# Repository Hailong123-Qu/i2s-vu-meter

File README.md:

Doesn't parse data during RMS calculation for about 108 ms

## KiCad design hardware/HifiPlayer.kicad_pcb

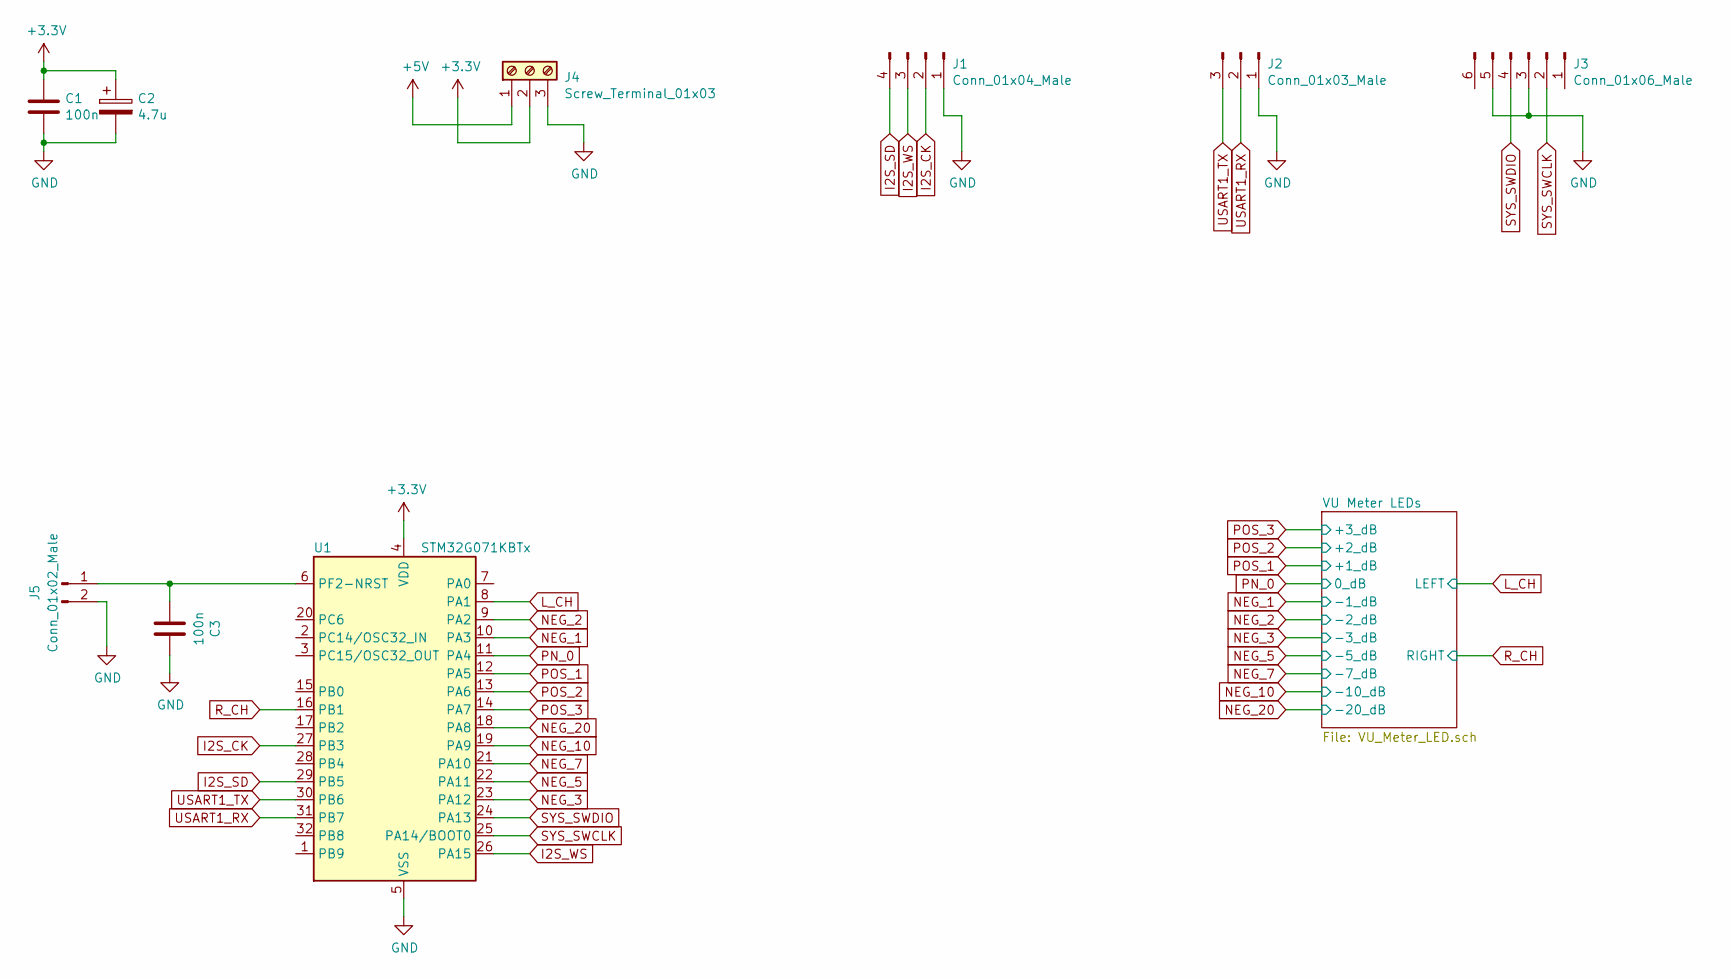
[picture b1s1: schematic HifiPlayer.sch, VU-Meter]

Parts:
C1, C3: 100n; C_1206_3216Metric_Pad1.42x1.75mm_HandSolder
C2: 4.7u; CP_Radial_D5.0mm_P2.00mm
J1: Conn_01x04_Male; PinHeader_1x04_P2.54mm_Vertical
J2: Conn_01x03_Male; PinHeader_1x03_P2.54mm_Vertical
J3: Conn_01x06_Male; PinHeader_1x06_P2.54mm_Vertical
J4: Screw_Terminal_01x03; TerminalBlock_bornier-3_P5.08mm
J5: Conn_01x02_Male; PinHeader_1x02_P2.54mm_Vertical
U1: STM32G071KBTx; LQFP-32_7x7mm_P0.8mm

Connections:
+3V3: C1.1, C2.1, J4.2, U1.4 (VDD)
+5V: J4.1; also elsewhere on the board
GND: C1.2, C2.2, C3.1, J1.1, J2.1, J3.3, J3.5, J4.3, J5.2, U1.5 (VSS); also elsewhere on the board
I2S_CK: J1.2, U1.27 (PB3)
I2S_SD: J1.4, U1.29 (PB5)
I2S_WS: J1.3, U1.26 (PA15)
L_CH: U1.8 (PA1); also elsewhere on the board
NEG_1: U1.10 (PA3); also elsewhere on the board
NEG_2: U1.9 (PA2); also elsewhere on the board
NEG_3: U1.23 (PA12); also elsewhere on the board
NEG_5: U1.22 (PA11); also elsewhere on the board
NEG_7: U1.21 (PA10); also elsewhere on the board
NEG_10: U1.19 (PA9); also elsewhere on the board
NEG_20: U1.18 (PA8); also elsewhere on the board
unnamed: C3.2, J5.1, U1.6 (PF2-NRST)
PN_0: U1.11 (PA4); also elsewhere on the board
POS_1: U1.12 (PA5); also elsewhere on the board
POS_2: U1.13 (PA6); also elsewhere on the board
POS_3: U1.14 (PA7); also elsewhere on the board
R_CH: U1.16 (PB1); also elsewhere on the board
SYS_SWCLK: J3.2, U1.25 (PA14/BOOT0)
SYS_SWDIO: J3.4, U1.24 (PA13)
USART1_RX: J2.2, U1.31 (PB7)
USART1_TX: J2.3, U1.30 (PB6)

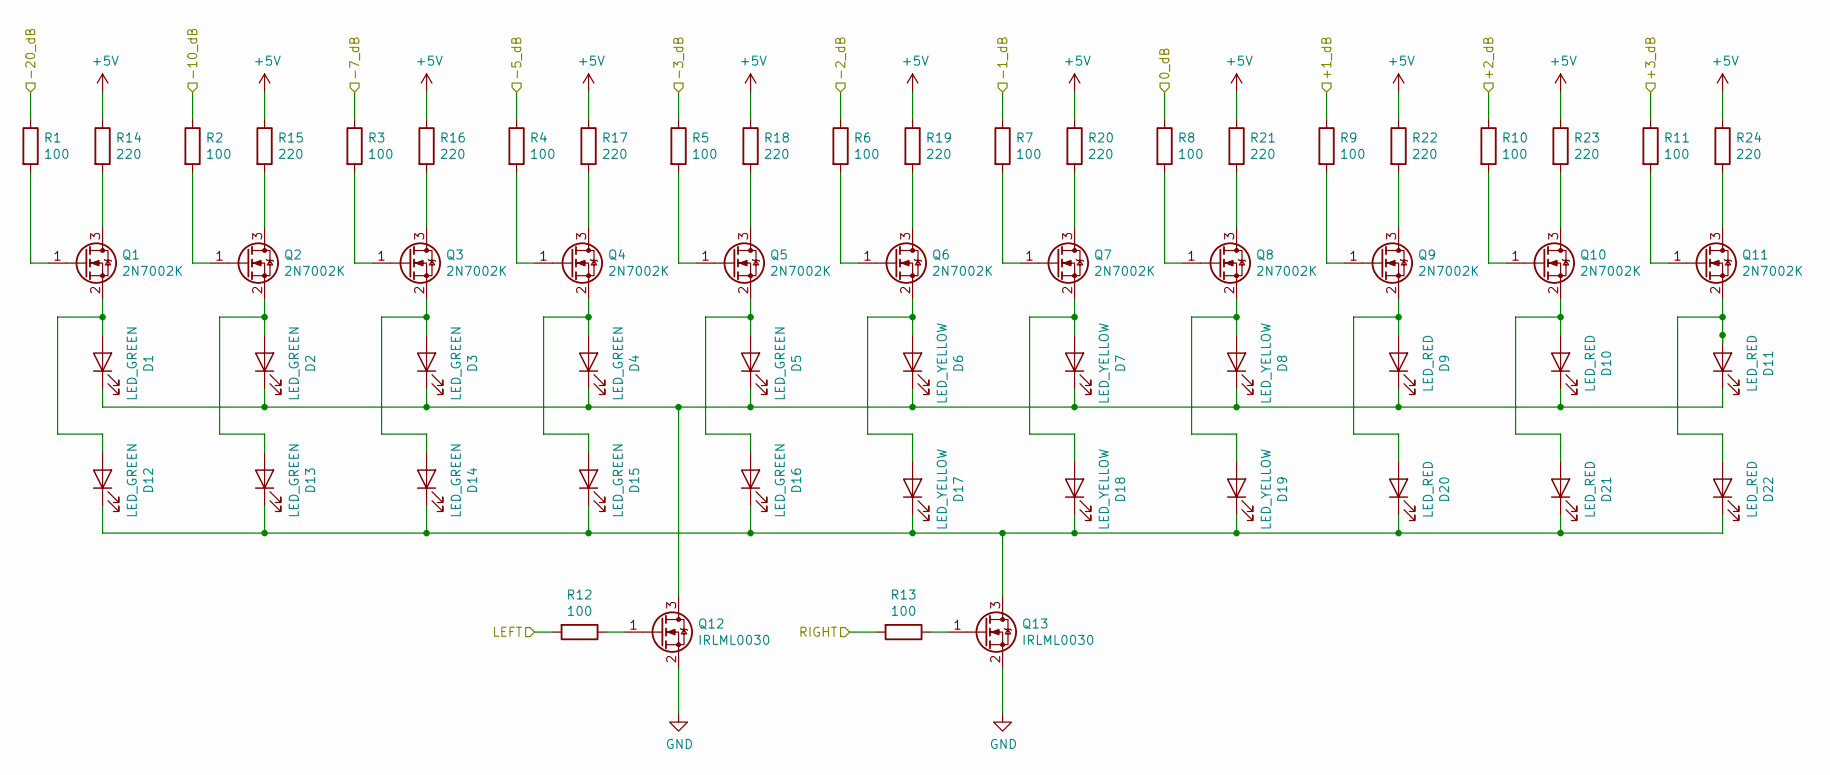
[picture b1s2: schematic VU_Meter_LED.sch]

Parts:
D1, D2, D3, D4, D5, D12, D13, D14, D15, D16: LED_GREEN; LED_D5.0mm
D6, D7, D8, D17, D18, D19: LED_YELLOW; LED_D5.0mm
D9, D10, D11, D20, D21, D22: LED_RED; LED_D5.0mm
Q1, Q2, Q3, Q4, Q5, Q6, Q7, Q8, Q9, Q10, Q11: 2N7002K; SOT-23_Handsoldering
Q12, Q13: IRLML0030; SOT-23_Handsoldering
R1, R2, R3, R4, R5, R6, R7, R8, R9, R10, R11, R12, R13: 100; R_1206_3216Metric_Pad1.42x1.75mm_HandSolder
R14, R15, R16, R17, R18, R19, R20, R21, R22, R23, R24: 220; R_Axial_DIN0207_L6.3mm_D2.5mm_P10.16mm_Horizontal

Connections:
+5V: R14.1, R15.1, R16.1, R17.1, R18.1, R19.1, R20.1, R21.1, R22.1, R23.1, R24.1; also elsewhere on the board
GND: Q12.2 (S), Q13.2 (S); also elsewhere on the board
L_CH: R12.2; also elsewhere on the board
NEG_1: R7.1; also elsewhere on the board
NEG_2: R6.1; also elsewhere on the board
NEG_3: R5.1; also elsewhere on the board
NEG_5: R4.1; also elsewhere on the board
NEG_7: R3.1; also elsewhere on the board
NEG_10: R2.1; also elsewhere on the board
NEG_20: R1.1; also elsewhere on the board
unnamed: D1.1 (K), D2.1 (K), D3.1 (K), D4.1 (K), D5.1 (K), D6.1 (K), D7.1 (K), D8.1 (K), D9.1 (K), D10.1 (K), D11.1 (K), Q12.3 (D)
unnamed: D1.2 (A), D12.2 (A), Q1.2 (S)
unnamed: D10.2 (A), D21.2 (A), Q10.2 (S)
unnamed: D11.2 (A), D22.2 (A), Q11.2 (S)
unnamed: D12.1 (K), D13.1 (K), D14.1 (K), D15.1 (K), D16.1 (K), D17.1 (K), D18.1 (K), D19.1 (K), D20.1 (K), D21.1 (K), D22.1 (K), Q13.3 (D)
unnamed: D2.2 (A), D13.2 (A), Q2.2 (S)
unnamed: D3.2 (A), D14.2 (A), Q3.2 (S)
unnamed: D4.2 (A), D15.2 (A), Q4.2 (S)
unnamed: D5.2 (A), D16.2 (A), Q5.2 (S)
unnamed: D6.2 (A), D17.2 (A), Q6.2 (S)
unnamed: D7.2 (A), D18.2 (A), Q7.2 (S)
unnamed: D8.2 (A), D19.2 (A), Q8.2 (S)
unnamed: D9.2 (A), D20.2 (A), Q9.2 (S)
unnamed: Q1.1 (G), R1.2
unnamed: Q1.3 (D), R14.2
unnamed: Q2.1 (G), R2.2
unnamed: Q2.3 (D), R15.2
unnamed: Q3.1 (G), R3.2
unnamed: Q3.3 (D), R16.2
unnamed: Q4.1 (G), R4.2
unnamed: Q4.3 (D), R17.2
unnamed: Q5.1 (G), R5.2
unnamed: Q5.3 (D), R18.2
unnamed: Q6.1 (G), R6.2
unnamed: Q6.3 (D), R19.2
unnamed: Q7.1 (G), R7.2
unnamed: Q7.3 (D), R20.2
unnamed: Q8.1 (G), R8.2
unnamed: Q8.3 (D), R21.2
unnamed: Q9.1 (G), R9.2
unnamed: Q9.3 (D), R22.2
unnamed: Q10.1 (G), R10.2
unnamed: Q10.3 (D), R23.2
unnamed: Q11.1 (G), R11.2
unnamed: Q11.3 (D), R24.2
unnamed: Q12.1 (G), R12.1
unnamed: Q13.1 (G), R13.1
PN_0: R8.1; also elsewhere on the board
POS_1: R9.1; also elsewhere on the board
POS_2: R10.1; also elsewhere on the board
POS_3: R11.1; also elsewhere on the board
R_CH: R13.2; also elsewhere on the board

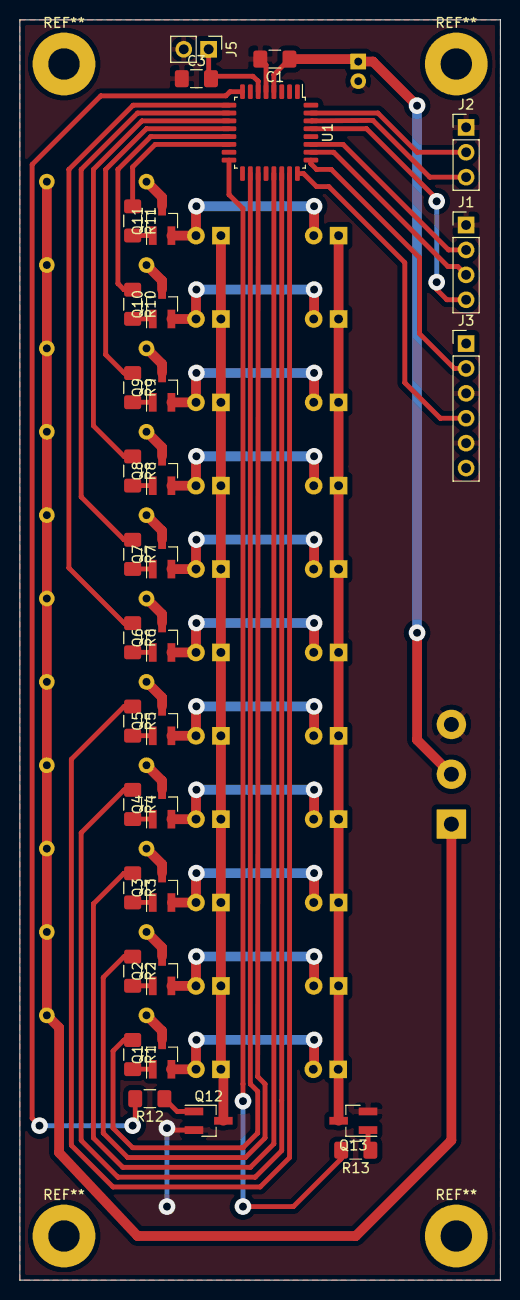
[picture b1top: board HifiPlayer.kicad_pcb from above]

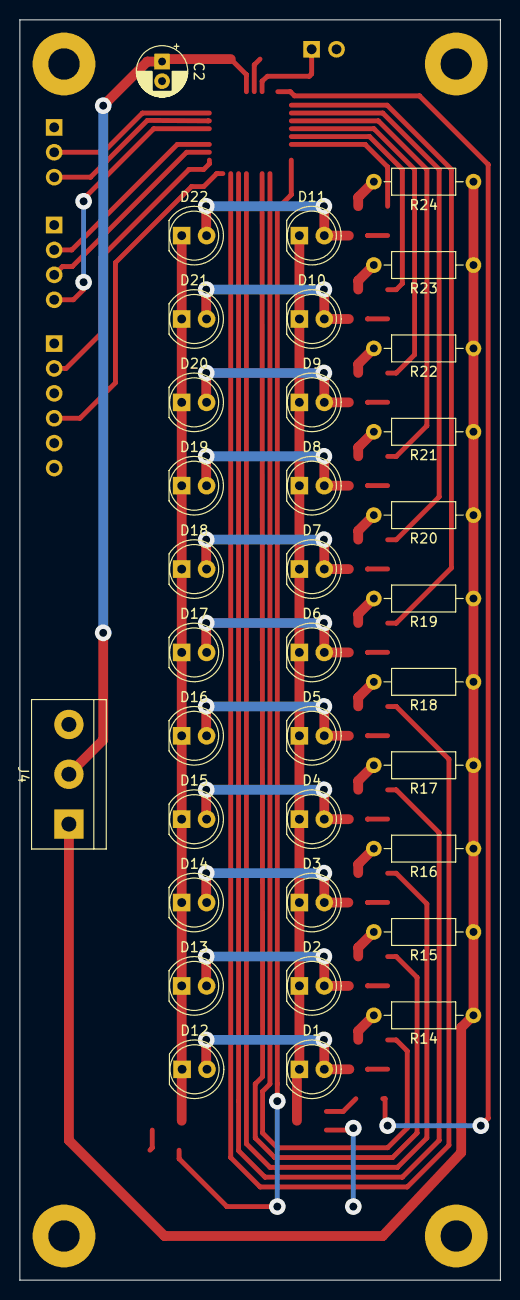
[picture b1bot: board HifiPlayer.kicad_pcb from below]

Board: 2 copper layers, 49.0 x 128.5 mm, 68 parts (35 on the bottom side), 61 nets.

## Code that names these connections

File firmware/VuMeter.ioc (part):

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Mcu.Name=STM32G071R(6-8-B)Tx
Mcu.Package=LQFP64
Mcu.UserName=STM32G071RBTx
PA1.Mode=Half_Duplex_Slave
PA1.Signal=I2S1_CK
PA10.GPIOParameters=GPIO_Label
PA10.GPIO_Label=n10Pin
PA10.Signal=GPIO_Output
PA2.Mode=Asynchronous
PA2.Signal=USART2_TX
PA3.Mode=Asynchronous
PA3.Signal=USART2_RX
PA4.Mode=Half_Duplex_Slave
PA4.Signal=I2S1_WS
PA5.Signal=GPIO_Output
PA6.GPIOParameters=GPIO_Label
PA6.GPIO_Label=p3Pin
PA6.Signal=GPIO_Output
PA7.GPIOParameters=GPIO_Label
PA7.GPIO_Label=p2Pin
PA7.Signal=GPIO_Output
PA8.GPIOParameters=GPIO_Label
PA8.GPIO_Label=n2Pin
PA8.Signal=GPIO_Output
PA9.GPIOParameters=GPIO_Label
PA9.GPIO_Label=n1Pin
PA9.Signal=GPIO_Output
PB0.GPIOParameters=GPIO_Label
PB0.GPIO_Label=p1Pin
PB0.Signal=GPIO_Output
PB14.GPIOParameters=GPIO_Label
PB14.GPIO_Label=n3Pin
PB14.Signal=GPIO_Output
PB3.GPIOParameters=GPIO_Label
PB3.GPIO_Label=n7Pin
PB3.Signal=GPIO_Output
PB4.GPIOParameters=GPIO_Label
PB4.GPIO_Label=n5Pin
PB4.Signal=GPIO_Output
PB5.Mode=Half_Duplex_Slave
PB5.Signal=I2S1_SD
PC4.GPIOParameters=GPIO_Label
PC4.GPIO_Label=n20Pin
PC4.Signal=GPIO_Output
PC7.GPIOParameters=GPIO_Label
PC7.GPIO_Label=pn0Pin
PC7.Signal=GPIO_Output
RCC.HSE_VALUE=8000000
RCC.SYSCLKFreq_VALUE=16000000
board=NUCLEO-G071RB

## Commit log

2020-03-23 Add led rows and STM32G071K
2020-03-23 Finished first draft
2020-03-23 Created STM project
2020-03-27 First layout
2020-03-27 Nope, not good
2020-03-27 Removed firmware
2020-03-27 Add empty STM32Cube project for Nucleo board
2020-03-27 Led is blinking
2020-04-01 LED blinks to I2S DMA
2020-04-01 UART works
2020-04-01 UART sends I2S stuff
2020-04-01 Add python parsing script for serial data
2020-04-02 Add sample buffer
2020-04-03 Migrated to new version of STM32Cube
2020-04-03 Changed protocol to Philps standard
2020-04-03 Added right channel
2020-04-03 Cleaned code a little bit
2020-04-03 Add README
2020-04-03 Control leds
2020-04-05 Increase sample time and change threshold
2020-04-09 Removed RMS calculation
2020-04-09 Remove CMSIS DSP
2020-04-09 Finished PCD Mk.1
2020-04-14 Cleanup
